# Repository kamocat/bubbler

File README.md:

# bubbler
A water level sensor using the bubbler technique

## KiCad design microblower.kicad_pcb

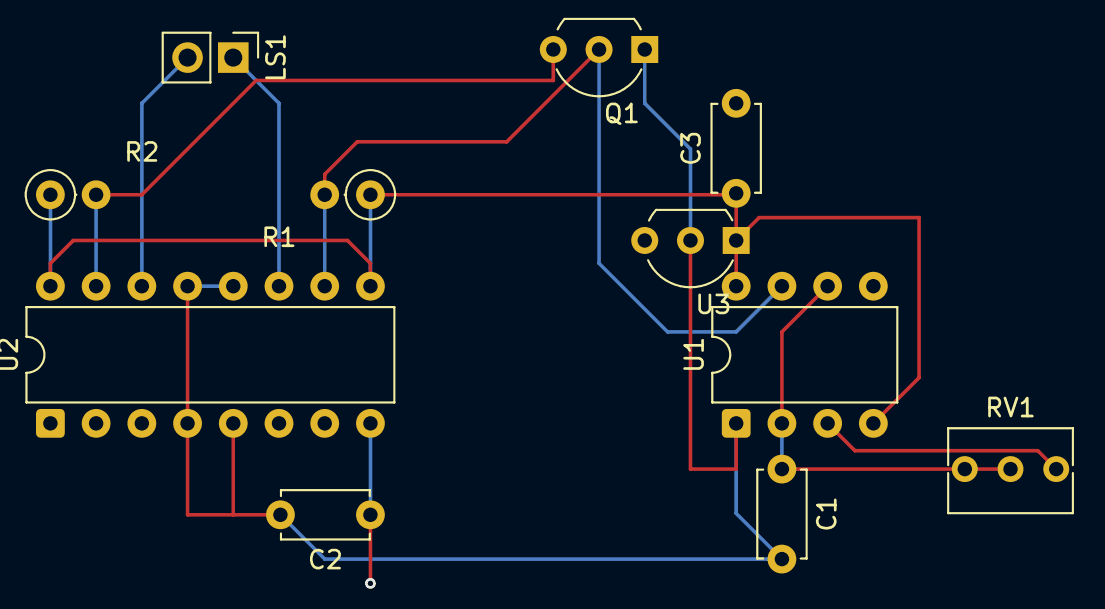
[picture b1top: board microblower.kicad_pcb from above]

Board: 2 copper layers, 11 parts (0 on the bottom side), 8 nets.

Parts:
C1: 1n; C_Disc_D4.7mm_W2.5mm_P5.00mm
C2, C3: 1u; C_Disc_D4.7mm_W2.5mm_P5.00mm
LS1: microblower; PinHeader_1x02_P2.54mm_Vertical
Q1: 2N7000; TO-92L_Inline_Wide
R1, R2: 10k; R_Axial_DIN0207_L6.3mm_D2.5mm_P2.54mm_Vertical
RV1: 5k; Potentiometer_Bourns_3266Y_Vertical
U1: NE555P; DIP-8_W7.62mm
U2: L293; DIP-16_W7.62mm
U3: L78L05_TO92; TO-92L_Inline_Wide

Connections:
+5V: C3.1, R1.1, R2.1, U1.4 (R), U1.8 (VCC), U2.9 (EN3,4), U2.16 (VCC1), U3.1 (VO)
+12V: C2.1, U2.8 (VCC2), U3.3 (VI)
GND: C1.2, C2.2, C3.2, Q1.1 (S), U1.1 (GND), U2.4 (GND), U2.5 (GND), U2.12 (GND), U2.13 (GND), U3.2 (GND)
unnamed: Q1.3 (D), R2.2, U2.15 (4A)
unnamed: Q1.2 (G), R1.2, U1.7 (DIS), U2.10 (3A)
unnamed: C1.1, RV1.2, RV1.3, U1.2 (TR), U1.6 (THR)
unnamed: LS1.1, U2.11 (3Y)
unnamed: LS1.2, U2.14 (4Y)

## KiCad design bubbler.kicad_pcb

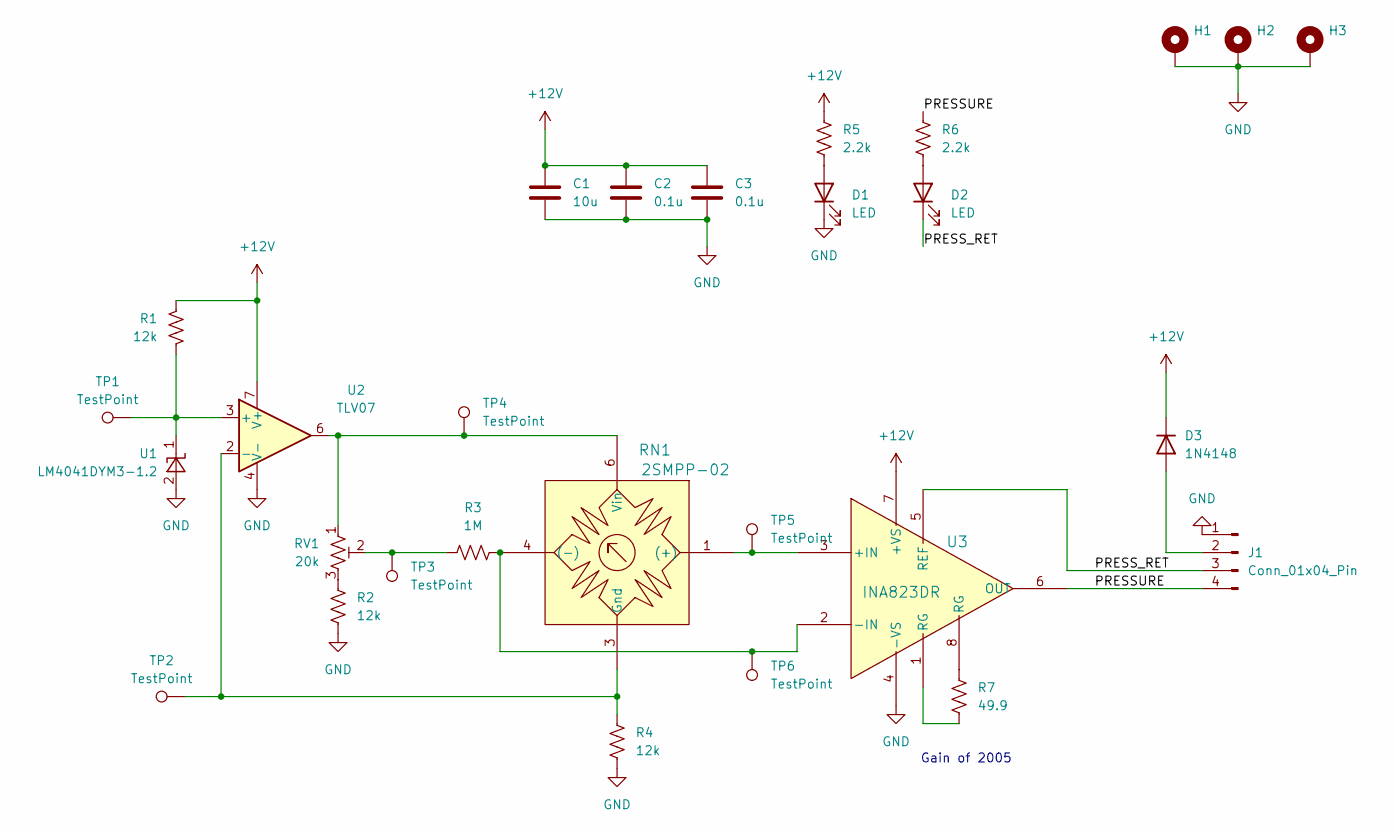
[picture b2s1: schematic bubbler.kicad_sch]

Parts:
C1: 10u; C_1206_3216Metric
C2: 0.1u; C_0603_1608Metric
C3: 0.1u; C_0805_2012Metric
D1, D2: LED; LED_0805_2012Metric
D3: 1N4148; D_DO-35_SOD27_P7.62mm_Horizontal
H1, H2, H3: MountingHole_Pad; MountingHole_3.2mm_M3_DIN965_Pad
J1: Conn_01x04_Pin; PinHeader_1x04_P2.54mm_Vertical
R1, R2, R4: 12k; R_0805_2012Metric
R3: 1M; R_0805_2012Metric
R5, R6: 2.2k; R_0603_1608Metric
R7: 49.9; R_0805_2012Metric
RN1: 2SMPP-02; 2SMPP-02_OMR
RV1: 20k; Potentiometer_Bourns_3266Z_Horizontal
TP1, TP2, TP3, TP4, TP5, TP6: TestPoint; TestPoint_Keystone_5015_Micro_Mini
U1: LM4041DYM3-1.2; SOT-23
U2: TLV07; SOIC-8_3.9x4.9mm_P1.27mm
U3: INA823DR; SOIC-8_5.3x6.2mm_P1.27mm

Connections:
+12V: C1.1, C2.1, C3.1, D3.1 (K), R1.1, R5.1, U2.7 (V+), U3.7 (+VS)
/PRESSURE: J1.4, R6.1, U3.6 (OUT)
/PRESS_RET: D2.1 (K), J1.3, U3.5 (REF)
GND: C1.2, C2.2, C3.2, D1.1 (K), H1.1, H2.1, H3.1, J1.1, R2.2, R4.2, U1.2 (A), U2.4 (V-), U3.4 (-VS)
unnamed: D1.2 (A), R5.2
unnamed: D2.2 (A), R6.2
unnamed: D3.2 (A), J1.2
unnamed: R2.1, RV1.3
unnamed: R3.1, RV1.2, TP3.1
unnamed: R7.1, U3.8 (RG)
unnamed: R7.2, U3.1 (RG)
unnamed: RN1.1 ((+)), TP5.1, U3.3 (+IN)
unnamed: R3.2, RN1.4 ((-)), TP6.1, U3.2 (-IN)
unnamed: R4.1, RN1.3 (Gnd), TP2.1, U2.2 (-)
unnamed: RN1.6 (Vin), RV1.1, TP4.1, U2.6
unnamed: R1.2, TP1.1, U1.1 (K), U2.3 (+)

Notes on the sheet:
Gain of 2005

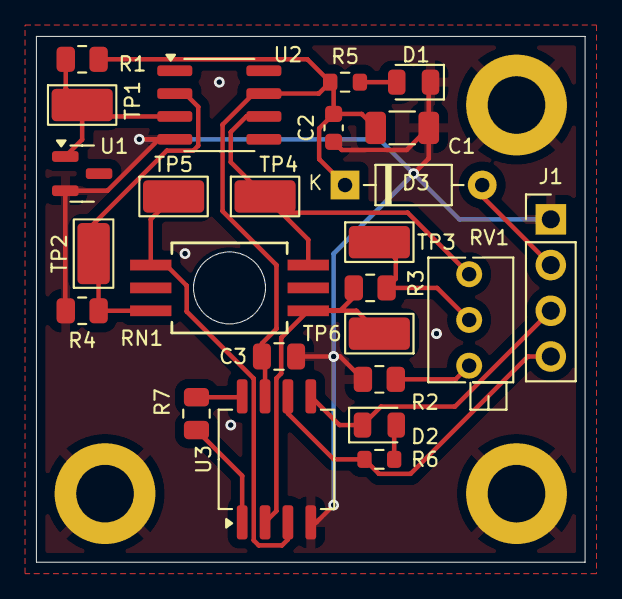
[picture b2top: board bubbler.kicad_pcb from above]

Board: 2 copper layers, 30.5 x 29.2 mm, 28 parts (0 on the bottom side), 16 nets.

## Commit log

2025-04-26 Tried basic pierce oscillator
    Didn't have enough phase shift
    I think the feedback resistor is misplaced
    No way to drive the second side of the invertere
2025-04-26 Switched to relaxation oscillator
2025-05-04 Settled on design for microblower
